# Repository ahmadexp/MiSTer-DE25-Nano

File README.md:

# MiSTer platform port for the DE25-Nano

This repository contains an independent MiSTer platform port for the Terasic
DE25-Nano and its Agilex 5 A5EB013 FPGA. It provides the shared Platform V2
board shell, Menu port, core compatibility patches, build automation, runtime
loader, SD-card tooling, hardware documentation, and a growing catalog of
ported MiSTer cores.

This is active bring-up work, not an official MiSTer distribution. A successful
Quartus build or guarded FPGA load does not by itself establish complete game,
BIOS, controller, video-mode, or audio compatibility.

## Current core status

| Core | Build and timing | Hardware gate |
| --- | --- | --- |
| Menu V2 | pass | boots on DE25-Nano |
| Apple I | pass | packaged |
| Atari 7800 / 2600 | pass | guarded load passed |
| ao486 | pass | content test pending |
| IBM PC/XT | pass | content test pending |
| IBM PC110 | pass | Personaware boots; corrected scaler active |
| Atari Jaguar | pass | guarded load passed; content pending |
| Minimig | pass | packaged |
| Nintendo 64 | pass | hardware load pending |
| NES | pass | packaged |
| PlayStation | pass | guarded load passed; BIOS/content pending |
| Sega Master System / Game Gear | pass | content test pending |
| Sega Saturn LIGHT | pass | hardware load pending |
| SNES | pass | packaged |
| TurboGrafx-16 | pass | packaged |

The exact candidate status, resource use, timing margins, and artifact hashes
are recorded in [`mister-de25/CORE_CANDIDATE_STATUS.md`](mister-de25/CORE_CANDIDATE_STATUS.md).

## Repository layout

- `mister-de25/`: Platform V2, Quartus projects, core patches, build scripts,
  Linux runtime integration, SD-card tooling, and tests.
- `hardware/de25-nano-bridge/`: KiCad source, reference Gerbers, and installation
  documentation for the passive GPIO 1 to Si5332B I2C bridge.
- `de25-nano/`: low-level board bring-up, Terasic GHRD import, and Si5332
  diagnostic projects.
- `shared/mister/`: shared upstream MiSTer framework sources needed by bundled
  platform integrations.

All core repositories, including IBM PC110, are fetched at pinned identities
during the build flow and patched locally when necessary. Generated upstream
checkouts, Quartus databases, ROMs, disk images, and private cartridge content
are intentionally excluded from version control.

## Platform V2

Platform V2 standardizes the DE25-Nano boundary used by Menu and all ported
cores:

- an immutable Terasic HPS partition reused across personas;
- the FDCD HPS I/O compatibility identity;
- common HPS DDR, native SDRAM, HDMI, audio, input, and runtime-loader wiring;
- exact Agilex 5 PLL projects and static timing constraints;
- guarded loading with automatic recovery to Menu;
- read-only Si5332 detection and clock monitoring.

Si5332 programming remains disabled until board-specific profiles and rollback
behavior are validated. Cores currently use their checked Agilex PLL paths.

See [`mister-de25/PLATFORM_V2.md`](mister-de25/PLATFORM_V2.md) and
[`mister-de25/SI5332B.md`](mister-de25/SI5332B.md) for the design details.

The optional passive bridge PCB makes the otherwise unconnected U24 SDA and
SCL pads available to the FPGA through GPIO 1 pins 1 and 2. Its source and
verified electrical mapping are documented in
[`hardware/de25-nano-bridge/README.md`](hardware/de25-nano-bridge/README.md).

## Building

Quartus Prime Pro 25.3.1 with Agilex 5 device support is the validated toolchain.
The build scripts can use a native installation or the configured Quartus
container image.

Prepare the licensed Terasic rev-B GHRD and the exact upstream source revisions
before the first build:

```sh
de25-nano/scripts/import-terasic-ghrd.sh /path/to/DE25-Nano_revB_v.1.0.0_ResourcePackage.zip
mister-de25/scripts/fetch-main-mister.sh
mister-de25/scripts/fetch-core-catalog.sh
```

The fetch scripts refuse to overwrite modified checkouts. Upstream trees are
kept under the ignored `mister-de25/upstream/` directory and the DE25 changes
remain reviewable as patch series in this repository.

```sh
mister-de25/scripts/test.sh
mister-de25/scripts/build-menu-v2.sh
mister-de25/scripts/build-nes-v2.sh
mister-de25/scripts/build-pcxt-v2.sh
mister-de25/scripts/build-sms-v2.sh
mister-de25/scripts/build-ao486-v2.sh
```

Large-core entry points are:

```sh
mister-de25/scripts/build-atari7800-v2.sh
mister-de25/scripts/build-jaguar-v2.sh
mister-de25/scripts/build-psx-v2.sh
mister-de25/scripts/build-n64-v2.sh
mister-de25/scripts/build-saturn-v2.sh
```

Every release build must pass synthesis, fitting, assembly, static timing,
SDRAM I/O timing, HPS I/O hash validation, and RBF digest generation.

## Installing

Verified candidate bundles are published under GitHub Releases. The updater
stages and verifies the complete bundle before changing the target and retains
the previous installation for rollback.

On an already migrated FDCD system:

```sh
sudo /media/fat/Scripts/update_de25.sh /path/to/extracted-update-bundle
sudo reboot
```

The first migration from another HPS I/O identity requires the matching
HPS-first QSPI image and a physical power cycle. Do not bypass the compatibility
interlock.

## Licensing

The repository license is in [`LICENSE`](LICENSE). Upstream projects retain
their own licenses and copyright notices. See
[`THIRD_PARTY_NOTICES.md`](THIRD_PARTY_NOTICES.md) and the source repositories
recorded in `mister-de25/official-core-catalog.tsv`.

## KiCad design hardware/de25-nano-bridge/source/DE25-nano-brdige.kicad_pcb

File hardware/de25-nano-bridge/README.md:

# DE25-Nano Si5332B I2C bridge

This directory contains the passive adapter PCB used to connect the DE25-Nano
Si5332B clock generator's U24 SDA and SCL test pads to FPGA GPIO 1. The board
spans GPIO 0 and GPIO 1 for mechanical alignment, while only two GPIO 1 pins
are electrically connected.

## Electrical mapping

| Signal | Bridge path | FPGA ball |
| --- | --- | --- |
| SDA | GPIO 1 connector J4 pin 1, R1 1 kOhm, SDA connector J1 | `BV14` |
| SCL | GPIO 1 connector J4 pin 2, R2 1 kOhm, SCL connector J2 | `CG26` |

The GPIO 0 connector J3 has no electrical connections. It is retained only to
locate and support the adapter. The bridge does not route power or ground and
does not add pull-up resistors. It relies on the DE25-Nano's common ground and
the existing 3.3 V I2C pull-ups. FPGA firmware must therefore use open-drain
behavior and must never actively drive SDA or SCL high.

Platform V2 keeps clock-generator writes disabled until a complete profile for
the detected Si5332 variant has been validated. The bridge does not change that
safety boundary.

## Files

- `source/`: KiCad 10 schematic, PCB, and project source.
- `gerbers/`: the supplied copper, mask, paste, silkscreen, outline, and Gerber
  job exports.
- `images/`: top, perspective, and installed-placement reference images.

The original project filenames contain the spelling `brdige`; they are retained
unchanged so the KiCad project continues to open without relinking its files.

## Manufacturing note

The supplied Gerber set does not contain an Excellon drill file, although the
design uses through-hole headers. Treat these Gerbers as reference exports.
Before ordering a PCB, open the source project in KiCad 10, run ERC and DRC,
regenerate the full fabrication package including plated drill data, and verify
the connector orientation against the installed-placement image.

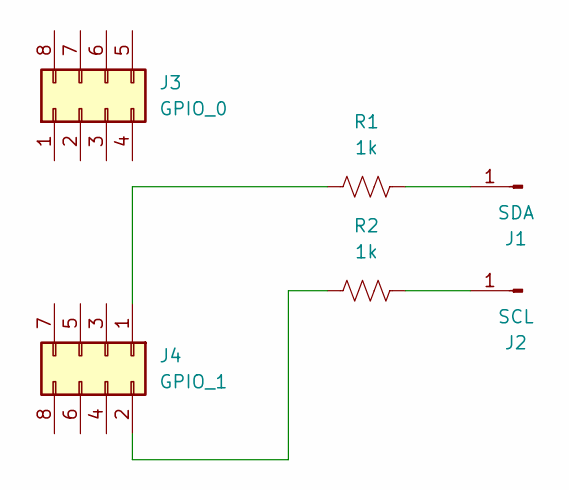
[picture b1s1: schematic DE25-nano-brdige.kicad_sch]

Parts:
J1: SDA; PinHeader_1x01_P1.00mm_Vertical
J2: SCL; PinHeader_1x01_P1.00mm_Vertical
J3: GPIO_0; PinHeader_2x04_P2.54mm_Vertical
J4: GPIO_1; PinHeader_2x04_P2.54mm_Vertical
R1, R2: 1k; R_0603_1608Metric

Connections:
unnamed: J1.1 (Pin_1_1), R1.2
unnamed: J2.1 (Pin_1_1), R2.2
unnamed: J4.1, R1.1
unnamed: J4.2, R2.1

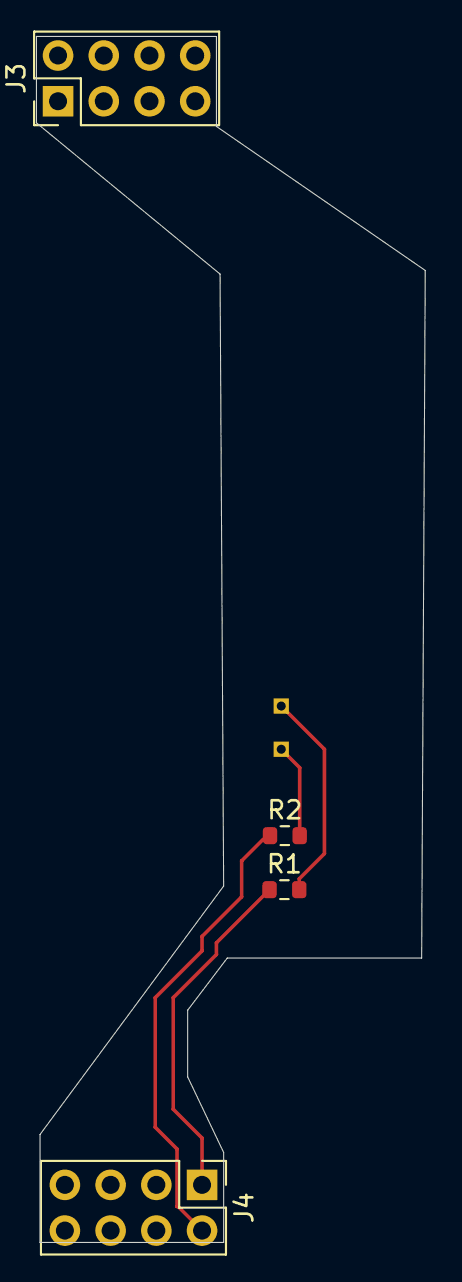
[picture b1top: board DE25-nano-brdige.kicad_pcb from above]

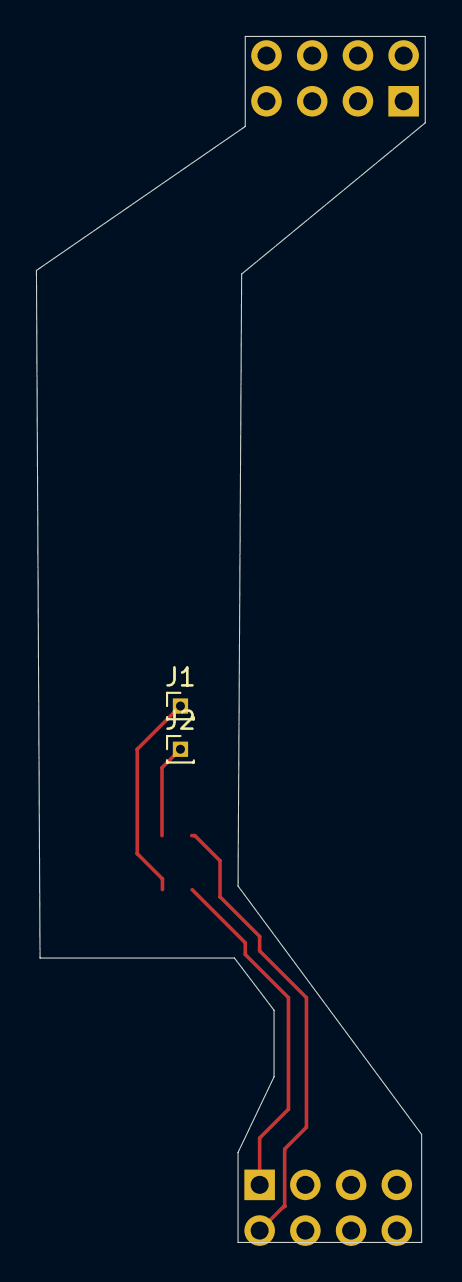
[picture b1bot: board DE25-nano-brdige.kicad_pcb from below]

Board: 2 copper layers, 21.6 x 67.0 mm, 6 parts (2 on the bottom side), 4 nets.
